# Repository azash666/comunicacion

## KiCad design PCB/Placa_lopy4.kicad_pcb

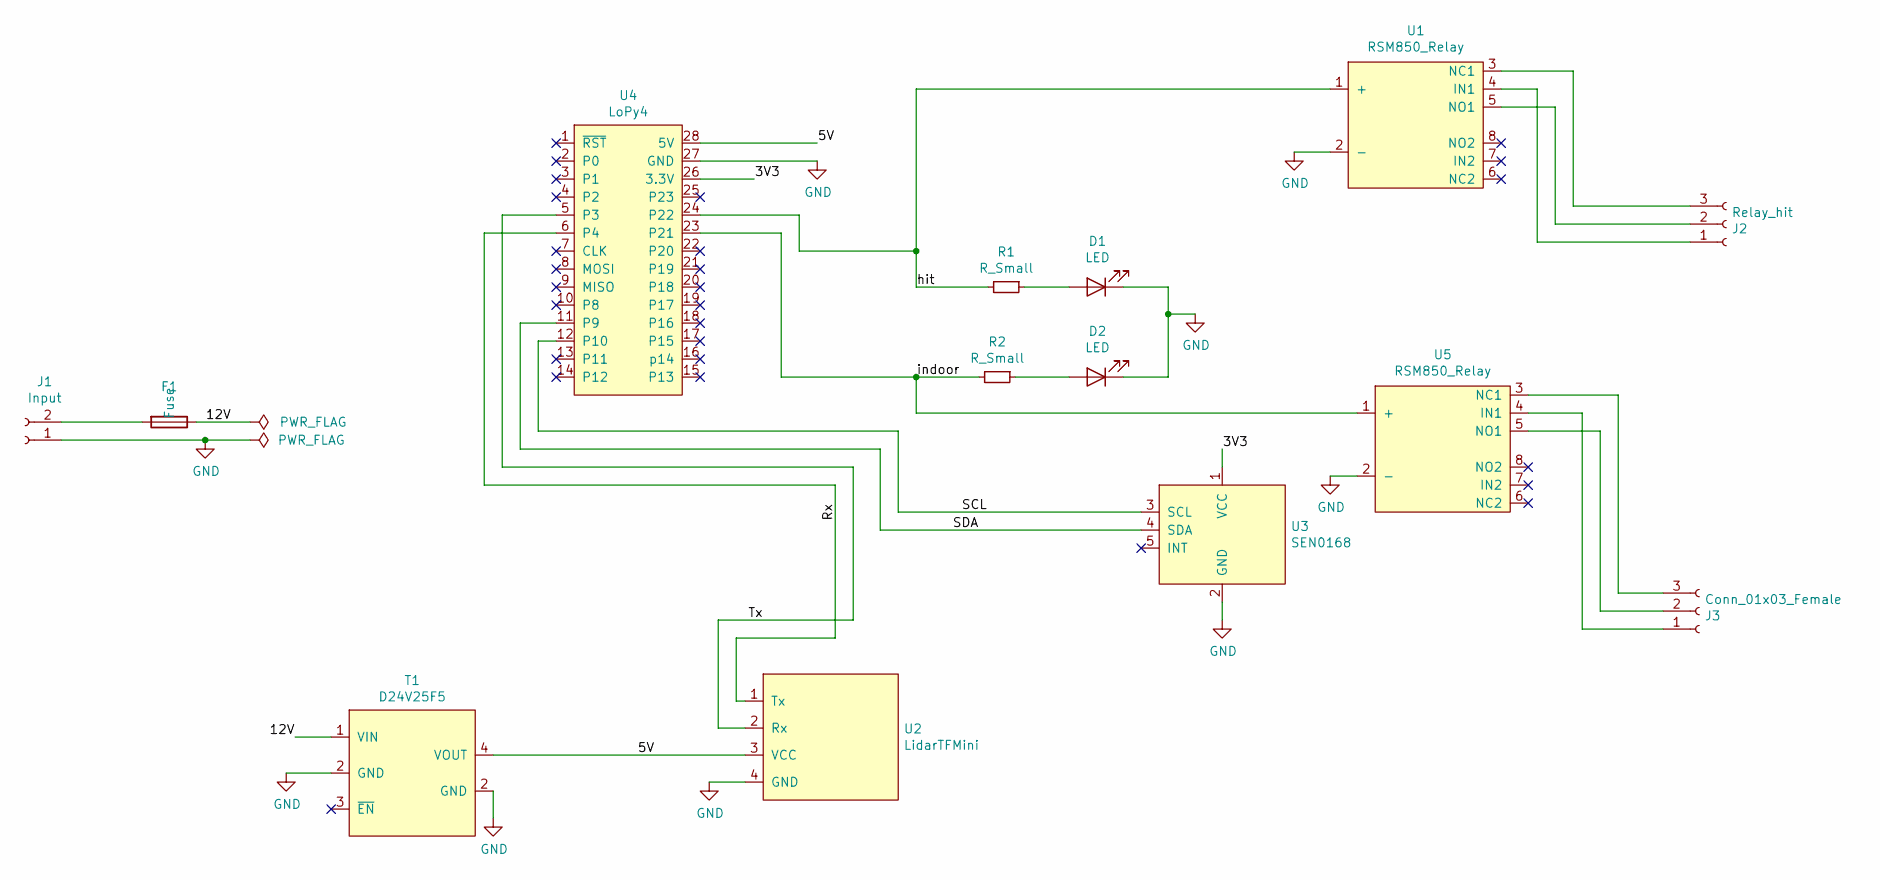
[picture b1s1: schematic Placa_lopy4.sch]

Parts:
D1, D2: LED; LED_D1.8mm_W3.3mm_H2.4mm
F1: Fuse; Fuseholder_Blade_ATO_Littelfuse_Pudenz_2_Pin
J1: Input; PinHeader_1x02_P2.54mm_Vertical
J2: Relay_hit; PinHeader_1x03_P2.54mm_Vertical
J3: Conn_01x03_Female; PinHeader_1x03_P2.54mm_Vertical
R1, R2: R_Small; R_Axial_DIN0204_L3.6mm_D1.6mm_P5.08mm_Horizontal
T1: D24V25F5; Transformer_Pololu_D24V25Fx
U1, U5: RSM850_Relay
U2: LidarTFMini; PinHeader_1x04_P2.54mm_Vertical
U3: SEN0168
U4: LoPy4

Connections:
/3V3: U3.1 (VCC), U4.26 (3.3V)
/5V: T1.4 (VOUT), U2.3 (VCC), U4.28 (5V)
/12V: F1.1, T1.1 (VIN)
/Rx: U2.1 (Tx), U4.6 (P4)
/SCL: U3.3 (SCL), U4.12 (P10)
/SDA: U3.4 (SDA), U4.11 (P9)
/Tx: U2.2 (Rx), U4.5 (P3)
/hit: R1.2, U1.1 (+), U4.24 (P22)
/indoor: R2.2, U4.23 (P21), U5.1 (+)
GND: D1.1 (K), D2.1 (K), J1.1, T1.2 (GND), U1.2 (-), U2.4 (GND), U3.2 (GND), U4.27 (GND), U5.2 (-); also elsewhere on the board
unnamed: D1.2 (A), R1.1
unnamed: D2.2 (A), R2.1
unnamed 12: F1.2, J1.2; also elsewhere on the board
unnamed: J2.1, U1.4 (IN1)
unnamed: J2.2, U1.5 (NO1)
unnamed: J2.3, U1.3 (NC1)
unnamed: J3.1, U5.4 (IN1)
unnamed: J3.2, U5.5 (NO1)
unnamed: J3.3, U5.3 (NC1)

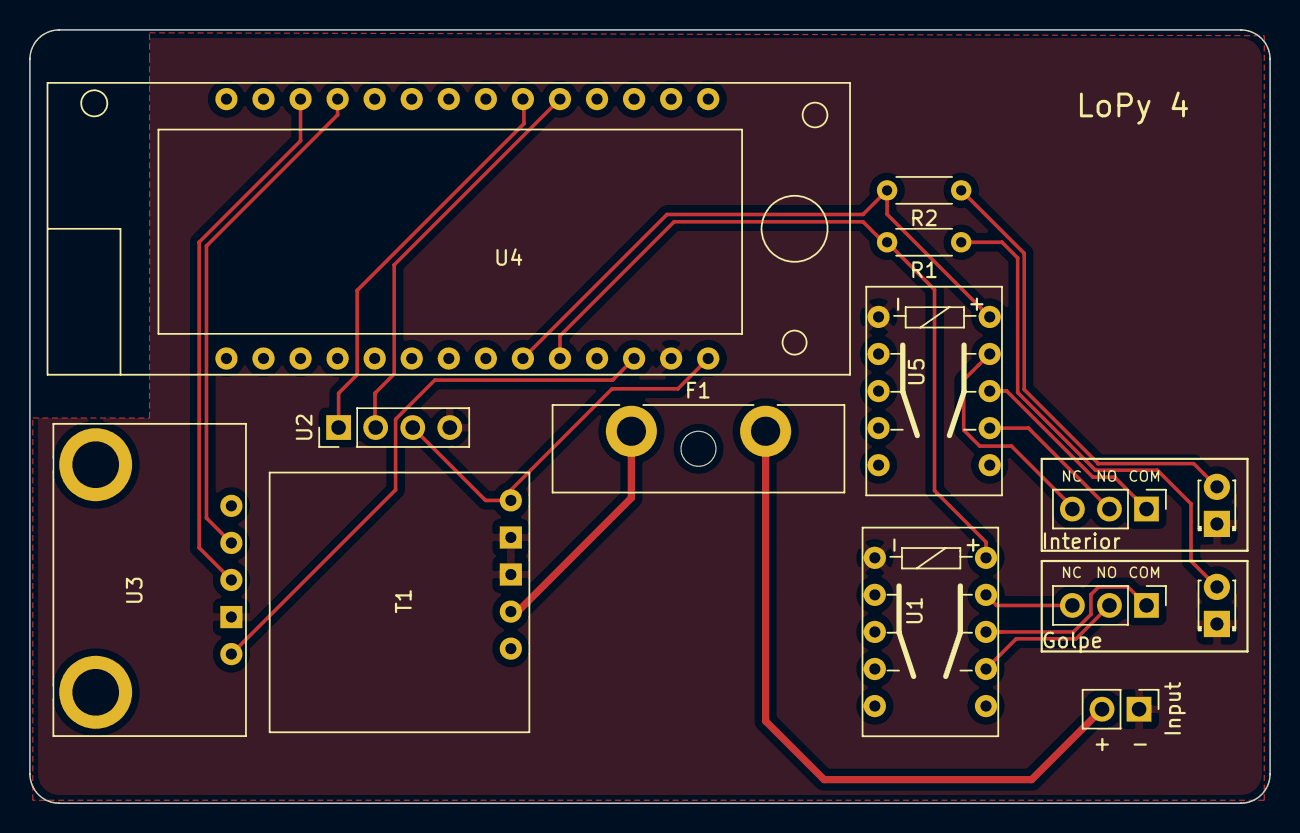
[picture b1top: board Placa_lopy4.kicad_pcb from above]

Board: 2 copper layers, 85.0 x 53.0 mm, 14 parts (0 on the bottom side), 19 nets.

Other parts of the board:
Input: Input; PinHeader_1x02_P2.54mm_Vertical

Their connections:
GND: Input.1; also elsewhere on the board
unnamed 12: Input.2; also elsewhere on the board
